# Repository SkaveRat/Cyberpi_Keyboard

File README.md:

# Cyberpi Keyboard

A keyboard PCB for an Atari Portfolio

Not a drop-in replacement for a Portfolio, as the flatflex cable is not at the right position. The pinout and key matrix is compatible, though.

## Atari Portfolio key matrix

| Pin |   1   |  2  |    3   |    4    |    5    |   6  |    7   |  8  |
|-----|-------|-----|--------|---------|---------|------|--------|-----|
| 9   | Atari |     |    1   |    2    |    3    |   D  |    5   |  6  |
| 10  |  Ins  | Alt |    Q   |    U    |    O    |   7  | Backsp |  9  |
| 11  |  Tab  |  W  | Ctrl L |    E    |    R    |   T  |  Enter |  Y  |
| 12  |   0   |  I  |    -   | Shift L |    L    |  Up  |    '   |  ]  |
| 13  |   S   |  P  |    4   |    G    | Shift R | Down |    ,   |  L  |
| 14  |   P   |  H  |    J   |  Left   | Right   | Caps |    8   |  K  |
| 15  |   \   |  Z  |  Space |    ;    |    .    |   =  |    Fn  |  X  |
| 16  |   C   |  V  |    B   |    N    |    M    |   /  |    A   | Esc |

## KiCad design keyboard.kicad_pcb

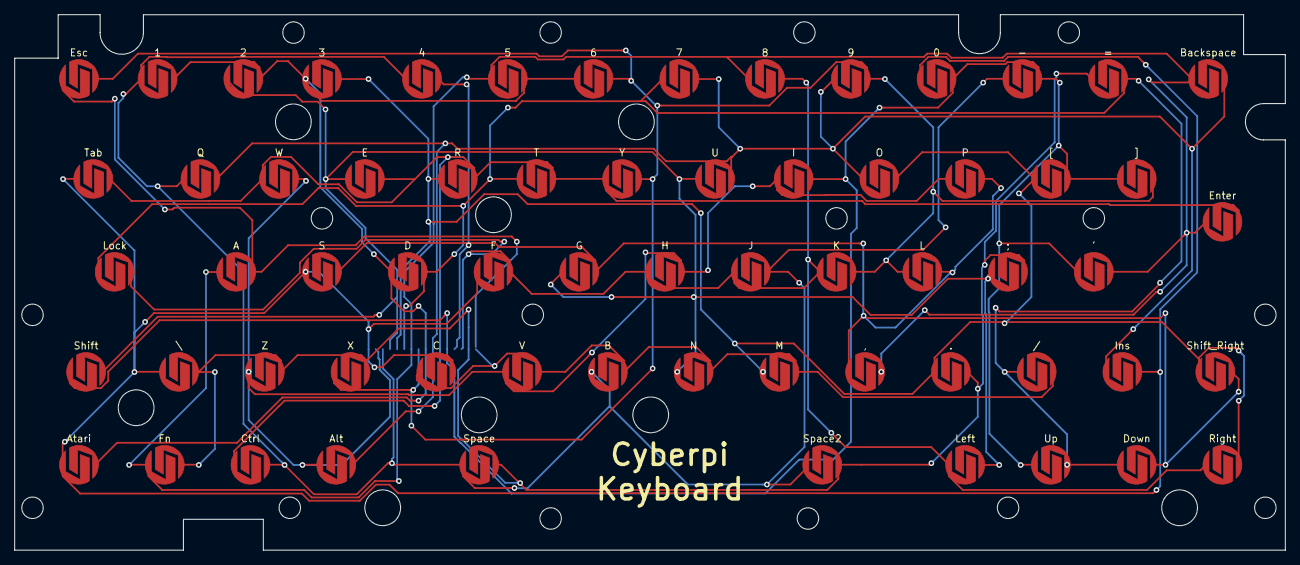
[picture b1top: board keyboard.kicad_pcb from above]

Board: 2 copper layers, 177.8 x 74.9 mm, 65 parts (1 on the bottom side), 16 nets.

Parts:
0: 0; SW_Push_Membrane
1: 1; SW_Push_Membrane
2: 2; SW_Push_Membrane
3: 3; SW_Push_Membrane
4: 4; SW_Push_Membrane
5: 5; SW_Push_Membrane
6: 6; SW_Push_Membrane
7: 7; SW_Push_Membrane
8: 8; SW_Push_Membrane
9: 9; SW_Push_Membrane
': '; SW_Push_Membrane
,: ,; SW_Push_Membrane
-: -; SW_Push_Membrane
.: .; SW_Push_Membrane
/: /; SW_Push_Membrane
;: ;; SW_Push_Membrane
=: =; SW_Push_Membrane
A: A; SW_Push_Membrane
Alt: Alt; SW_Push_Membrane
Atari: Atari; SW_Push_Membrane
B: B; SW_Push_Membrane
Backspace: Backspace; SW_Push_Membrane
C: C; SW_Push_Membrane
Ctrl: Ctrl; SW_Push_Membrane
D: D; SW_Push_Membrane
Down: Down; SW_Push_Membrane
E: E; SW_Push_Membrane
Enter: Enter; SW_Push_Membrane
Esc: Esc; SW_Push_Membrane
F: F; SW_Push_Membrane
Fn: Fn; SW_Push_Membrane
G: G; SW_Push_Membrane
H: H; SW_Push_Membrane
I: I; SW_Push_Membrane
Ins: Ins; SW_Push_Membrane
J: J; SW_Push_Membrane
J1: Conn_02x08_Odd_Even; TE_1-84953-6_1x16-1MP_P1.0mm_Horizontal
K: K; SW_Push_Membrane
L: L; SW_Push_Membrane
Left: Left; SW_Push_Membrane
Lock: Lock; SW_Push_Membrane
M: M; SW_Push_Membrane
N: N; SW_Push_Membrane
O: O; SW_Push_Membrane
P: P; SW_Push_Membrane
Q: Q; SW_Push_Membrane
R: R; SW_Push_Membrane
Right: Right; SW_Push_Membrane
S: S; SW_Push_Membrane
Shift: Shift; SW_Push_Membrane
Shift_Right: Shift_Right; SW_Push_Membrane
Space: Space; SW_Push_Membrane
Space2: Space2; SW_Push_Membrane
T: T; SW_Push_Membrane
Tab: Tab; SW_Push_Membrane
U: U; SW_Push_Membrane
Up: Up; SW_Push_Membrane
V: V; SW_Push_Membrane
W: W; SW_Push_Membrane
X: X; SW_Push_Membrane
Y: Y; SW_Push_Membrane
Z: Z; SW_Push_Membrane
[: [; SW_Push_Membrane
\: \; SW_Push_Membrane
]: ]; SW_Push_Membrane

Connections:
/1: 0.1, Atari.1, C.2, F.1, Ins.2, J1.1, S.1, Tab.1, \.1
/2: Alt.1, H.2, I.1, J1.2, P.1, V.1, W.2, Z.1
/3: 1.1, 4.1, -.1, B.1, Ctrl.2, J.2, J1.3, Q.1, Space.1, Space2.1
/4: 2.1, ;.1, E.1, G.1, J1.4, Left.2, N.1, Shift.2, U.1
/5: 3.2, ..1, J1.5, M.1, O.2, R.1, Right.2, Shift_Right.1, [.1
/6: 7.1, /.1, =.2, D.2, Down.1, J1.6, Lock.1, T.1, Up.2
/7: 5.1, 8.1, '.2, ,.2, A.1, Backspace.1, Enter.1, Fn.1, J1.7
/8: 6.2, 9.2, Esc.2, J1.8, K.2, L.1, X.1, Y.2, ].2
/9: 1.2, 2.2, 3.1, 5.2, 6.1, Atari.2, D.1, J1.9
/10: 7.2, 9.1, Alt.2, Backspace.2, Ins.1, J1.10, O.1, Q.2, U.2
/11: Ctrl.1, E.2, Enter.2, J1.11, R.2, T.2, Tab.2, W.1, Y.1
/12: 0.2, '.1, -.2, I.2, J1.12, Shift.1, Up.1, [.2, ].1
/13: 4.2, ,.1, Down.2, G.2, J1.13, L.2, P.2, S.2, Shift_Right.2
/14: 8.2, F.2, H.1, J.1, J1.14, K.1, Left.1, Lock.2, Right.1
/15: ..2, ;.2, =.1, Fn.2, J1.15, Space.2, Space2.2, X.2, Z.2, \.2
/16: /.2, A.2, B.2, C.1, Esc.1, J1.16, M.2, N.2, V.2

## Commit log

2022-04-27 init
2022-04-27 Initial version
2022-05-03 Adding readme and keyboard matrix
